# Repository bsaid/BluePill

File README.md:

# BluePill

This project is a mess and it has never been tested.

The goal is to make STM32F103C BluePill compatible PCB with safety resistors, robust power supply with protections and SD card addon using a stacked PCB. The project is designed in [KiCad](https://www.kicad.org/) with design rules for [JLCPCB](https://jlcpcb.com/) including SMT assembly with their LCSC parts library.

This PCB was never tested or manufactured because the STM32 microcontrollers are out of stock globally.

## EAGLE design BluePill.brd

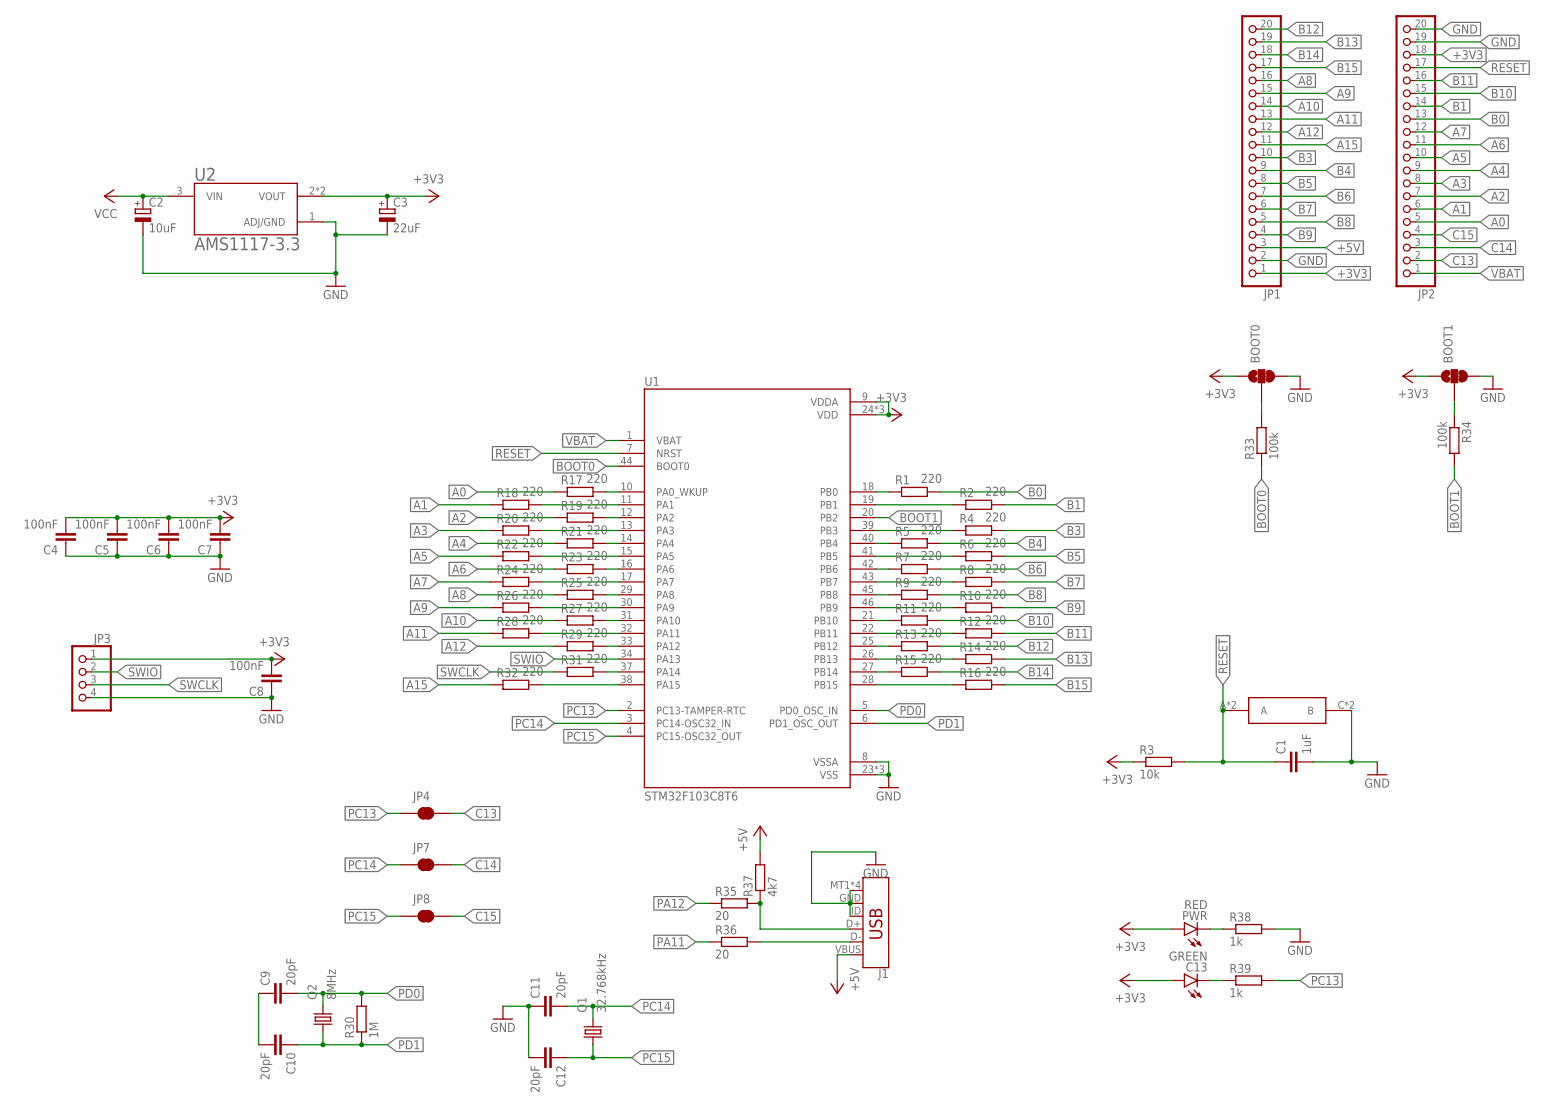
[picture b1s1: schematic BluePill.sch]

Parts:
BOOT0, BOOT1: JUMPER-SMT_3_1-NC_TRACE_NO-SILK; SMT-JUMPER_3_1-NC_TRACE_NO-SILK
C1: 1uF; C0402K; LCSC C52923
C2: 10uF; A/3216-18R; LCSC C7171
C3: 22uF; R/2012-12R; LCSC C147776
C4, C5: 100nF; C0402K; LCSC C1525
C6, C7, C8: 100nF; C0402K; LCSC C52923
C9, C10, C11, C12: 20pF; C0402K; LCSC C52923
C13: GREEN; SML0603; LCSC C72043
J1: USB_MICRO-B_SMT; USB-MICROB
JP1, JP2: PINHD-1X20; 1X20
JP3: PINHD-1X4; 1X04
JP4, JP7, JP8: JUMPER-SMT_2_NC_TRACE_SILK; SMT-JUMPER_2_NC_TRACE_SILK
PWR: RED; SML0603; LCSC C2286
Q1: 32.768kHz; 3.2X1.5; LCSC C32346
Q2: 8MHz; 5.0X3.2_2; LCSC C115962
R1, R2, R4, R5, R6, R7, R8, R9, R10, R11, R12, R13, R14, R15, R16, R17, R18, R19, R20, R21, R22, R23, R24, R25, R26, R27, R28, R29, R31, R32: 220; R0402; LCSC C25091
R3: 10k; R0402; LCSC C25744
R30: 1M; R0402; LCSC C26083
R33, R34: 100k; R0402; LCSC C25741
R35, R36: 20; R0402; LCSC C4109
R37: 4k7; R0402; LCSC C25900
R38, R39: 1k; R0402; LCSC C11702
U1: STM32F103C8T6; QFP50P900X900X160-48N
U2: AMS1117-3.3; SOT229P700X180-4N; LCSC C6186
U$1: TACTILE-SWITCH; TS-1187A-B-A-B; LCSC C318884

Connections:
+3V3: BOOT0.1, BOOT1.1, C3.+, C4.2, C5.2, C6.2, C7.2, C8.2, C13.A, JP1.1, JP2.18, JP3.1, PWR.A, R3.1, U1.9 (VDDA), U1.24 (VDD), U1.36 (VDD), U1.48 (VDD), U2.2 (VOUT), U2.4 (VOUT)
+5V: J1.VBUS, JP1.3, R37.2
A0: JP2.5, R17.1
A1: JP2.6, R18.1
A2: JP2.7, R19.1
A3: JP2.8, R20.1
A4: JP2.9, R21.1
A5: JP2.10, R22.1
A6: JP2.11, R23.1
A7: JP2.12, R24.1
A8: JP1.16, R25.1
A9: JP1.15, R26.1
A10: JP1.14, R27.1
A11: JP1.13, R28.1
A12: JP1.12, R29.1
A15: JP1.11, R32.1
B0: JP2.13, R1.2
B1: JP2.14, R2.2
B3: JP1.10, R4.2
B4: JP1.9, R5.2
B5: JP1.8, R6.2
B6: JP1.7, R7.2
B7: JP1.6, R8.2
B8: JP1.5, R9.2
B9: JP1.4, R10.2
B10: JP2.15, R11.2
B11: JP2.16, R12.2
B12: JP1.20, R13.2
B13: JP1.19, R14.2
B14: JP1.18, R15.2
B15: JP1.17, R16.2
BOOT0: R33.1, U1.44 (BOOT0)
BOOT1: R34.2, U1.20 (PB2)
C13: JP2.2, JP4.2
C14: JP2.3, JP7.2
C15: JP2.4, JP8.2
GND: BOOT0.3, BOOT1.3, C1.2, C2.-, C3.-, C4.1, C5.1, C6.1, C7.1, C8.1, C11.1, C12.2, J1.GND, J1.ID, J1.MT1 (SHIELD), J1.MT2 (SHIELD), J1.P$1 (SHIELD), J1.P$2 (SHIELD), JP1.2, JP2.19, JP2.20, JP3.4, R38.2, U1.8 (VSSA), U1.23 (VSS), U1.35 (VSS), U1.47 (VSS), U2.1 (ADJ/GND), U$1.C (B), U$1.D (B)
unnamed: BOOT0.2, R33.2
unnamed: BOOT1.2, R34.1
unnamed: R1.1, U1.18 (PB0)
unnamed: R2.1, U1.19 (PB1)
unnamed: C9.1, C10.2
unnamed: R4.1, U1.39 (PB3)
unnamed: R5.1, U1.40 (PB4)
unnamed: R6.1, U1.41 (PB5)
unnamed: R7.1, U1.42 (PB6)
unnamed: R8.1, U1.43 (PB7)
unnamed: R9.1, U1.45 (PB8)
unnamed: R10.1, U1.46 (PB9)
unnamed: R11.1, U1.21 (PB10)
unnamed: R12.1, U1.22 (PB11)
unnamed: R13.1, U1.25 (PB12)
unnamed: R14.1, U1.26 (PB13)
unnamed: R15.1, U1.27 (PB14)
unnamed: R16.1, U1.28 (PB15)
unnamed: PWR.C, R38.1
unnamed: C13.C, R39.1
unnamed: J1.D-, R36.2
unnamed: R17.2, U1.10 (PA0_WKUP)
unnamed: R18.2, U1.11 (PA1)
unnamed: R19.2, U1.12 (PA2)
unnamed: R20.2, U1.13 (PA3)
unnamed: R21.2, U1.14 (PA4)
unnamed: R22.2, U1.15 (PA5)
unnamed: R23.2, U1.16 (PA6)
unnamed: R24.2, U1.17 (PA7)
unnamed: R25.2, U1.29 (PA8)
unnamed: R26.2, U1.30 (PA9)
unnamed: R27.2, U1.31 (PA10)
unnamed: R31.2, U1.37 (PA14)
unnamed: R32.2, U1.38 (PA15)
unnamed: J1.D+, R35.2, R37.1
PA11: R28.2, R36.1, U1.32 (PA11)
PA12: R29.2, R35.1, U1.33 (PA12)
PC13: JP4.1, R39.2, U1.2 (PC13-TAMPER-RTC)
PC14: C11.2, JP7.1, Q1.2, U1.3 (PC14-OSC32_IN)
PC15: C12.1, JP8.1, Q1.1, U1.4 (PC15-OSC32_OUT)
PD0: C9.2, Q2.2, R30.2, U1.5 (PD0_OSC_IN)
PD1: C10.1, Q2.1, R30.1, U1.6 (PD1_OSC_OUT)
RESET: C1.1, JP2.17, R3.2, U1.7 (NRST), U$1.A, U$1.B (A)
SWCLK: JP3.3, R31.1
SWIO: JP3.2, U1.34 (PA13)
VBAT: JP2.1, U1.1 (VBAT)
VCC: C2.+, U2.3 (VIN)

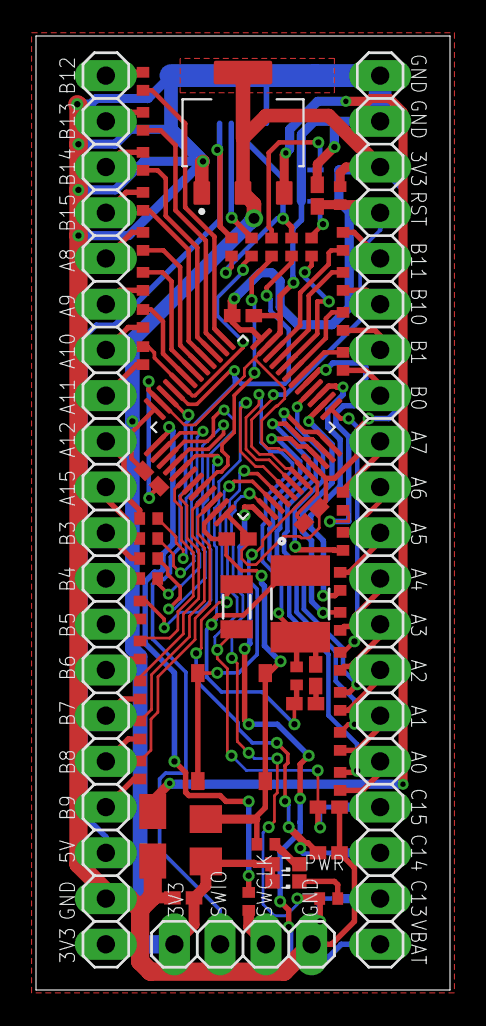
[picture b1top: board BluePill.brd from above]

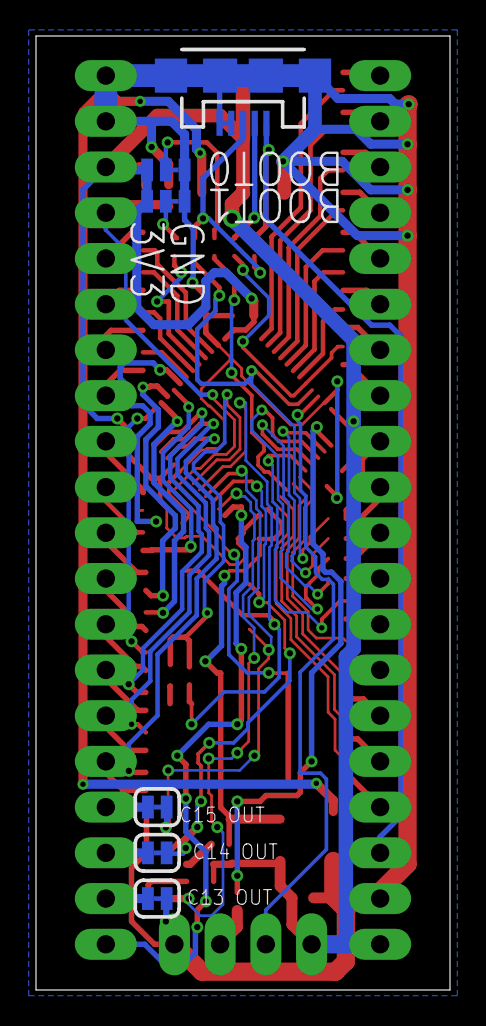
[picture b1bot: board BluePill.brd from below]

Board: 2 copper layers, 23.0 x 53.0 mm, 67 parts (6 on the bottom side), 84 nets.

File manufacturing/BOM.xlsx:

Comment | Designator | Footprint | LCSC
100k | R33, R34 | R0402 | C25741
100nF | C4, C5 | C0402K | C1525
100nF | C6, C7, C8 | C0402K | C52923
10k | R3 | R0402 | C25744
10uF | C2 | CASE-A_3216 | C7171
1M | R30 | R0402 | C26083
1k | R38, R39 | R0402 | C11702
1uF | C1 | C0402K | C52923
20 | R35, R36 | R0402 | C4109
20pF | C9, C10, C11, C12 | C0402K | C52923
220 | R1, R2, R4, R5, R6, R7, R8, R9, R10, R11, R12, R13, R14, R15, R16, R17, R18, R1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 | R0402 | C25091
22uF | C3 | CASE-R_2012 | C147776
32.768kHz | Q1 | SMD-3215_2P | C32346
4k7 | R37 | R0402 | C25900
8MHz | Q2 | SMD-5032_2P | C115962
AMS1117-3.3 | U2 | SOT-223 | C6186
GREEN | C13 | LED_0603 | C72043
RED | PWR | LED_0603 | C2286
STM32F103C8T6 | U1 | LQFP-48_7.0x7.0x0.5P | C8734
TACTILE-SWITCH | U$1 | SMD-SW-4_5.1x5.1x1.5 | C318884

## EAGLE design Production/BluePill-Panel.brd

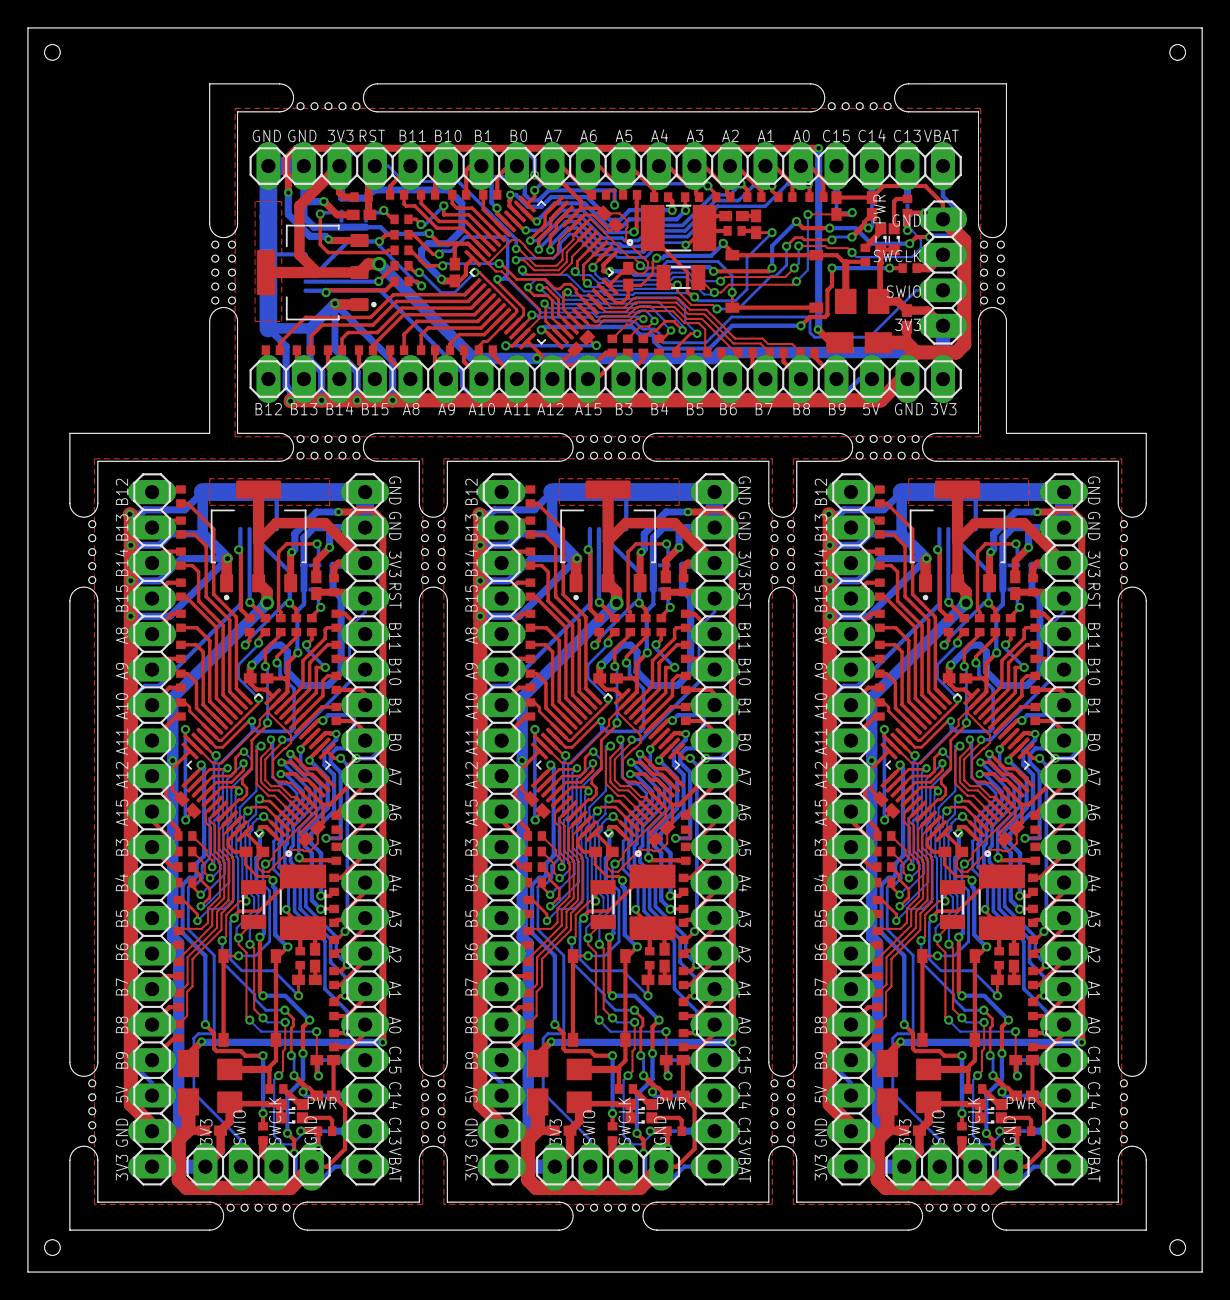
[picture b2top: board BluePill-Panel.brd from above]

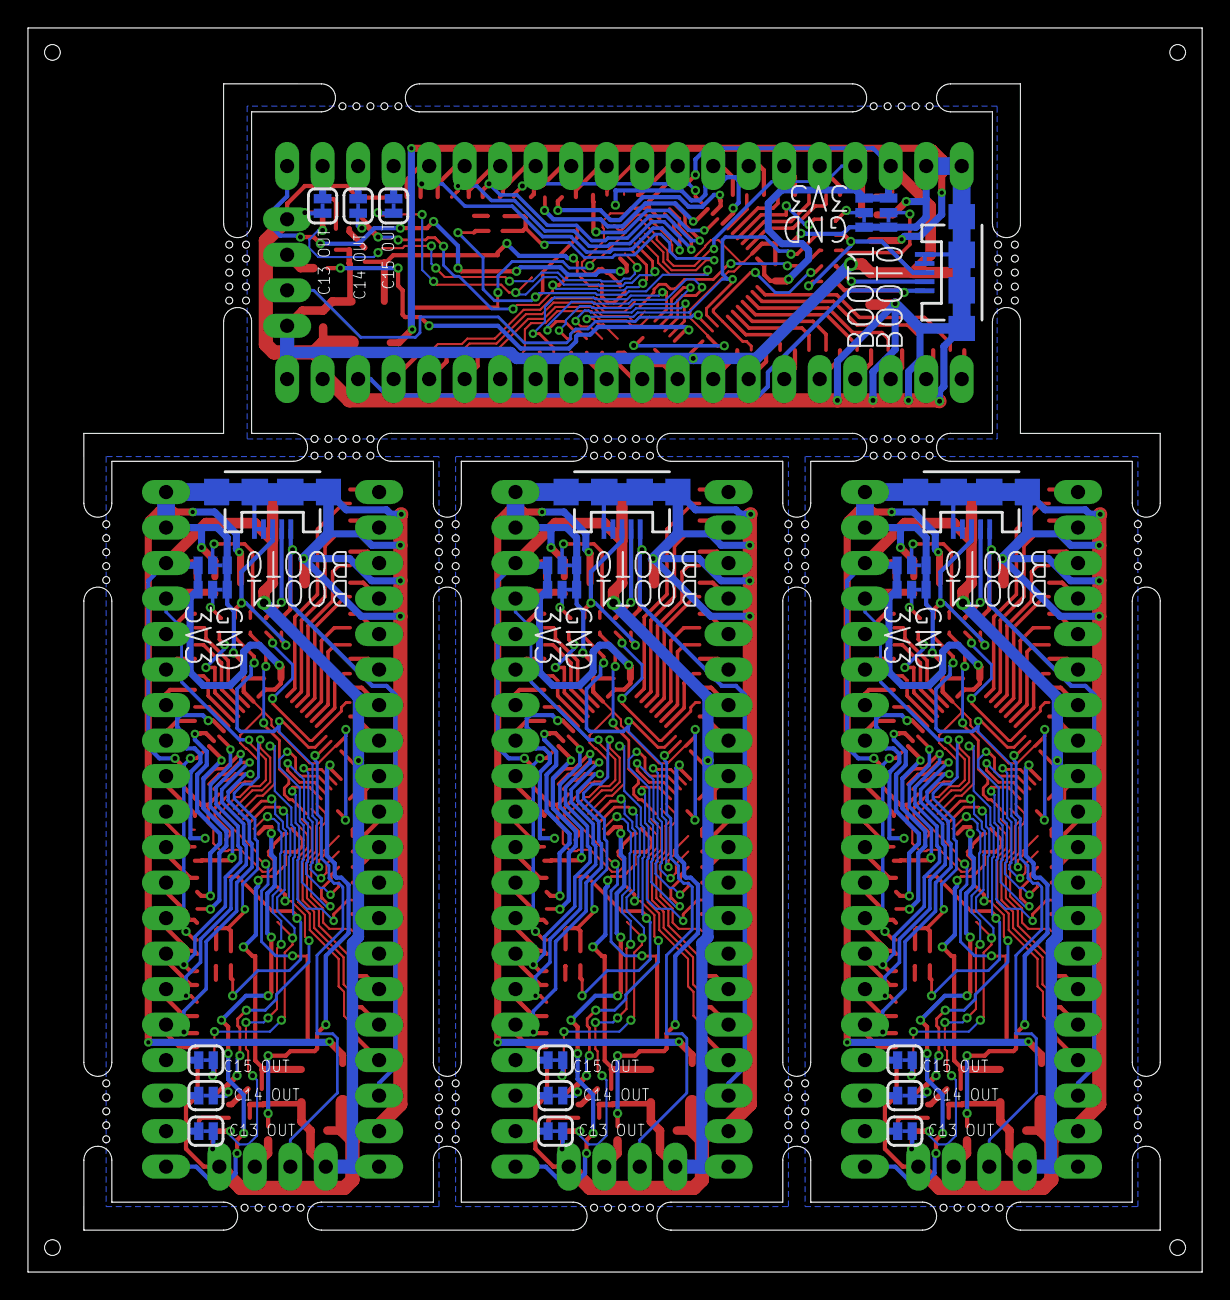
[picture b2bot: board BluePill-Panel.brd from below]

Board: 2 copper layers, 84.0 x 89.0 mm, 268 parts (24 on the bottom side), 336 nets.

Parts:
BOOT0, BOOT1, BOOT2, BOOT3, BOOT4, BOOT5, BOOT6, BOOT7: JUMPER-SMT_3_1-NC_TRACE_NO-SILK; SMT-JUMPER_3_1-NC_TRACE_NO-SILK
C1, C14, C27, C40: 1uF; C0402K
C2, C16, C29, C42: 10uF; A/3216-18R
C3, C15, C28, C41: 22uF; R/2012-12R
C4, C5, C6, C7, C8, C17, C18, C19, C20, C21, C30, C31, C32, C33, C34, C43, C44, C45, C46, C47: 100nF; C0402K
C9, C10, C11, C12, C22, C23, C24, C25, C35, C36, C37, C38, C48, C49, C50, C51: 20pF; C0402K
C13, C26, C39, C52: GREEN; SML0603
J1, J2, J3, J4: USB-MICROB
JP1, JP2, JP5, JP6, JP13, JP14, JP19, JP20: 1X20
JP3, JP9, JP15, JP21: 1X04
JP4, JP7, JP8, JP10, JP11, JP12, JP16, JP17, JP18, JP22, JP23, JP24: JUMPER-SMT_2_NC_TRACE_SILK; SMT-JUMPER_2_NC_TRACE_SILK
PWR, PWR1, PWR2, PWR3: RED; SML0603
Q1, Q3, Q5, Q7: 32.768kHz; 3.2X1.5
Q2, Q4, Q6, Q8: 8MHz; 5.0X3.2_2
R1, R2, R4, R5, R6, R7, R8, R9, R10, R11, R12, R13, R14, R15, R16, R17, R18, R19, R20, R21, R22, R23, R24, R25, R26, R27, R28, R29, R31, R32, R40, R41, R42, R43, R44, R45, R46, R47, R48, R49, R50, R51, R52, R53, R54, R55, R56, R57, R58, R59, R60, R61, R62, R63, R64, R65, R66, R67, R68, R69, R79, R80, R81, R82, R83, R84, R85, R86, R87, R88, R89, R90, R91, R92, R93, R94, R95, R96, R97, R98, R99, R100, R101, R102, R103, R104, R105, R106, R107, R108, R118, R119, R120, R121, R122, R123, R124, R125, R126, R127, R128, R129, R130, R131, R132, R133, R134, R135, R136, R137, R138, R139, R140, R141, R142, R143, R144, R145, R146, R147: 220; R0402
R3, R72, R111, R150: 10k; R0402
R30, R76, R115, R154: 1M; R0402
R33, R34, R70, R71, R109, R110, R148, R149: 100k; R0402
R35, R36, R73, R74, R112, R113, R151, R152: 20; R0402
R37, R75, R114, R153: 4k7; R0402
R38, R39, R77, R78, R116, R117, R155, R156: 1k; R0402
U1, U3, U5, U7: STM32F103C8T6; QFP50P900X900X160-48N
U2, U4, U6, U8: AMS1117-3.3; SOT229P700X180-4N
U$1, U$2, U$3, U$4: TACTILE-SWITCH; TS-1187A-B-A-B

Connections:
+3V1: BOOT2.1, BOOT3.1, C15.+, C17.2, C18.2, C19.2, C20.2, C21.2, C26.A, JP5.1, JP6.18, JP9.1, PWR1.A, R72.1, U3.9, U3.24, U3.36, U3.48, U4.2, U4.4
+3V2: BOOT4.1, BOOT5.1, C28.+, C30.2, C31.2, C32.2, C33.2, C34.2, C39.A, JP13.1, JP14.18, JP15.1, PWR2.A, R111.1, U5.9, U5.24, U5.36, U5.48, U6.2, U6.4
+3V3: BOOT0.1, BOOT1.1, C3.+, C4.2, C5.2, C6.2, C7.2, C8.2, C13.A, JP1.1, JP2.18, JP3.1, PWR.A, R3.1, U1.9, U1.24, U1.36, U1.48, U2.2, U2.4
+3V4: BOOT6.1, BOOT7.1, C41.+, C43.2, C44.2, C45.2, C46.2, C47.2, C52.A, JP19.1, JP20.18, JP21.1, PWR3.A, R150.1, U7.9, U7.24, U7.36, U7.48, U8.2, U8.4
+5V: J1.VBUS, JP1.3, R37.2
+5V1: J2.VBUS, JP5.3, R75.2
+5V2: J3.VBUS, JP13.3, R114.2
+5V3: J4.VBUS, JP19.3, R153.2
A0: JP2.5, R17.1
A1: JP2.6, R18.1
A2: JP2.7, R19.1
A3: JP2.8, R20.1
A4: JP2.9, R21.1
A5: JP2.10, R22.1
A6: JP2.11, R23.1
A7: JP2.12, R24.1
A8: JP1.16, R25.1
A9: JP1.15, R26.1
A10: JP1.14, R27.1
A11: JP1.13, R28.1
A12: JP1.12, R29.1
A13: JP6.5, R55.1
A14: JP6.7, R57.1
A15: JP1.11, R32.1
A16: JP6.9, R59.1
A17: JP6.11, R61.1
A18: JP5.16, R63.1
A19: JP5.14, R65.1
A20: JP5.12, R67.1
A21: JP6.6, R56.1
A22: JP6.8, R58.1
A23: JP6.10, R60.1
A24: JP6.12, R62.1
A25: JP5.15, R64.1
A26: JP5.13, R66.1
A27: JP5.11, R69.1
A28: JP14.5, R94.1
A29: JP14.7, R96.1
A30: JP14.9, R98.1
A31: JP14.11, R100.1
A32: JP13.16, R102.1
A33: JP13.14, R104.1
A34: JP13.12, R106.1
A35: JP14.6, R95.1
A36: JP14.8, R97.1
A37: JP14.10, R99.1
A38: JP14.12, R101.1
A39: JP13.15, R103.1
A40: JP13.13, R105.1
A41: JP13.11, R108.1
A42: JP20.5, R133.1
A43: JP20.7, R135.1
A44: JP20.9, R137.1
A45: JP20.11, R139.1
A46: JP19.16, R141.1
A47: JP19.14, R143.1
A48: JP19.12, R145.1
A49: JP20.6, R134.1
A50: JP20.8, R136.1
A51: JP20.10, R138.1
A52: JP20.12, R140.1
A53: JP19.15, R142.1
A54: JP19.13, R144.1
A55: JP19.11, R147.1
B0: JP2.13, R1.2
B1: JP2.14, R2.2
B2: JP6.13, R40.2
B3: JP1.10, R4.2
B4: JP1.9, R5.2
B5: JP1.8, R6.2
B6: JP1.7, R7.2
B7: JP1.6, R8.2
B8: JP1.5, R9.2
B9: JP1.4, R10.2
B10: JP2.15, R11.2
B11: JP2.16, R12.2
B12: JP1.20, R13.2
B13: JP1.19, R14.2
B14: JP1.18, R15.2
B15: JP1.17, R16.2
B16: JP6.14, R41.2
B17: JP5.10, R42.2
B18: JP5.9, R43.2
B19: JP5.7, R45.2
B20: JP5.8, R44.2
B21: JP5.6, R46.2
B22: JP5.5, R47.2
B23: JP6.15, R49.2
B24: JP5.4, R48.2
B25: JP5.20, R51.2
B26: JP6.16, R50.2
B27: JP5.19, R52.2
B28: JP5.18, R53.2
B29: JP5.17, R54.2
B30: JP14.13, R79.2
B31: JP14.14, R80.2
B32: JP13.10, R81.2
B33: JP13.9, R82.2
B34: JP13.7, R84.2
B35: JP13.8, R83.2
B36: JP13.6, R85.2
B37: JP13.5, R86.2
B38: JP14.15, R88.2
B39: JP13.4, R87.2
B40: JP13.20, R90.2
B41: JP14.16, R89.2
B42: JP13.19, R91.2
B43: JP13.18, R92.2
B44: JP13.17, R93.2
B45: JP20.13, R118.2
B46: JP20.14, R119.2
B47: JP19.10, R120.2
B48: JP19.9, R121.2
B49: JP19.7, R123.2
B50: JP19.8, R122.2
B51: JP19.6, R124.2
B52: JP19.5, R125.2
B53: JP20.15, R127.2
B54: JP19.4, R126.2
B55: JP19.20, R129.2
B56: JP20.16, R128.2
B57: JP19.19, R130.2
B58: JP19.18, R131.2
B59: JP19.17, R132.2
BOOT0: R33.1, U1.44
BOOT1: R34.2, U1.20
BOOT2: R70.1, U3.44
BOOT3: R71.2, U3.20
BOOT4: R109.1, U5.44
BOOT5: R110.2, U5.20
BOOT6: R148.1, U7.44
BOOT7: R149.2, U7.20
C1: JP6.4, JP12.2
C2: JP6.2, JP10.2
C3: JP6.3, JP11.2
C4: JP14.4, JP18.2
C5: JP14.2, JP16.2
C6: JP14.3, JP17.2
C7: JP20.4, JP24.2
C8: JP20.2, JP22.2
C9: JP20.3, JP23.2
C13: JP2.2, JP4.2
C14: JP2.3, JP7.2
C15: JP2.4, JP8.2
GND: BOOT0.3, BOOT1.3, C1.2, C2.-, C3.-, C4.1, C5.1, C6.1, C7.1, C8.1, C11.1, C12.2, J1.GND, J1.ID, J1.MT1, J1.MT2, J1.P$1, J1.P$2, JP1.2, JP2.19, JP2.20, JP3.4, R38.2, U1.8, U1.23, U1.35, U1.47, U2.1, U$1.C, U$1.D
GND1: BOOT2.3, BOOT3.3, C14.2, C15.-, C16.-, C17.1, C18.1, C19.1, C20.1, C21.1, C24.1, C25.2, J2.GND, J2.ID, J2.MT1, J2.MT2, J2.P$1, J2.P$2, JP5.2, JP6.19, JP6.20, JP9.4, R77.2, U3.8, U3.23, U3.35, U3.47, U4.1, U$2.C, U$2.D
GND2: BOOT4.3, BOOT5.3, C27.2, C28.-, C29.-, C30.1, C31.1, C32.1, C33.1, C34.1, C37.1, C38.2, J3.GND, J3.ID, J3.MT1, J3.MT2, J3.P$1, J3.P$2, JP13.2, JP14.19, JP14.20, JP15.4, R116.2, U5.8, U5.23, U5.35, U5.47, U6.1, U$3.C, U$3.D
GND3: BOOT6.3, BOOT7.3, C40.2, C41.-, C42.-, C43.1, C44.1, C45.1, C46.1, C47.1, C50.1, C51.2, J4.GND, J4.ID, J4.MT1, J4.MT2, J4.P$1, J4.P$2, JP19.2, JP20.19, JP20.20, JP21.4, R155.2, U7.8, U7.23, U7.35, U7.47, U8.1, U$4.C, U$4.D
unnamed: BOOT0.2, R33.2
unnamed: BOOT1.2, R34.1
unnamed: R1.1, U1.18
unnamed: R2.1, U1.19
unnamed: C9.1, C10.2
unnamed: R4.1, U1.39
unnamed: R5.1, U1.40
unnamed: R6.1, U1.41
unnamed: R7.1, U1.42
unnamed: R8.1, U1.43
unnamed: R9.1, U1.45
unnamed: R10.1, U1.46
unnamed: R11.1, U1.21
unnamed: R12.1, U1.22
unnamed: R13.1, U1.25
unnamed: R14.1, U1.26
unnamed: R15.1, U1.27
unnamed: R16.1, U1.28
unnamed: PWR.C, R38.1
unnamed: C13.C, R39.1
unnamed: R40.1, U3.18
unnamed: R41.1, U3.19
unnamed: R42.1, U3.39
unnamed: R43.1, U3.40
unnamed: J1.D-, R36.2
unnamed: R17.2, U1.10
unnamed: R18.2, U1.11
unnamed: R19.2, U1.12
unnamed: R20.2, U1.13
unnamed: R21.2, U1.14
unnamed: R22.2, U1.15
unnamed: R23.2, U1.16
unnamed: R24.2, U1.17
unnamed: R25.2, U1.29
unnamed: R26.2, U1.30
unnamed: R27.2, U1.31
unnamed: R44.1, U3.41
unnamed: R45.1, U3.42
unnamed: R46.1, U3.43
unnamed: R31.2, U1.37
unnamed: R32.2, U1.38
unnamed: R47.1, U3.45
unnamed: R48.1, U3.46
unnamed: R49.1, U3.21
unnamed: J1.D+, R35.2, R37.1
unnamed: R50.1, U3.22
unnamed: R51.1, U3.25
unnamed: R52.1, U3.26
unnamed: R53.1, U3.27
unnamed: R54.1, U3.28
unnamed: R55.2, U3.10
unnamed: R56.2, U3.11
unnamed: R57.2, U3.12
unnamed: R58.2, U3.13
unnamed: R59.2, U3.14
unnamed: R60.2, U3.15
unnamed: R61.2, U3.16
unnamed: R62.2, U3.17
unnamed: R63.2, U3.29
unnamed: R64.2, U3.30
unnamed: R65.2, U3.31
unnamed: R68.2, U3.37
unnamed: R69.2, U3.38
unnamed: BOOT2.2, R70.2
unnamed: BOOT3.2, R71.1
unnamed: J2.D-, R74.2
unnamed: J2.D+, R73.2, R75.1
unnamed: C22.1, C23.2
unnamed: PWR1.C, R77.1
unnamed: C26.C, R78.1
unnamed: R79.1, U5.18
unnamed: R80.1, U5.19
unnamed: R81.1, U5.39
unnamed: R82.1, U5.40
unnamed: R83.1, U5.41
unnamed: R84.1, U5.42
unnamed: R85.1, U5.43
unnamed: R86.1, U5.45
unnamed: R87.1, U5.46
unnamed: R88.1, U5.21
unnamed: R89.1, U5.22
unnamed: R90.1, U5.25
unnamed: R91.1, U5.26
unnamed: R92.1, U5.27
unnamed: R93.1, U5.28
unnamed: R94.2, U5.10
unnamed: R95.2, U5.11
unnamed: R96.2, U5.12
unnamed: R97.2, U5.13
unnamed: R98.2, U5.14
unnamed: R99.2, U5.15
unnamed: R100.2, U5.16
unnamed: R101.2, U5.17
unnamed: R102.2, U5.29
unnamed: R103.2, U5.30
unnamed: R104.2, U5.31
unnamed: R107.2, U5.37
unnamed: R108.2, U5.38
unnamed: BOOT4.2, R109.2
unnamed: BOOT5.2, R110.1
unnamed: J3.D-, R113.2
unnamed: J3.D+, R112.2, R114.1
unnamed: C35.1, C36.2
unnamed: PWR2.C, R116.1
unnamed: C39.C, R117.1
unnamed: R118.1, U7.18
unnamed: R119.1, U7.19
unnamed: R120.1, U7.39
unnamed: R121.1, U7.40
unnamed: R122.1, U7.41
unnamed: R123.1, U7.42
unnamed: R124.1, U7.43
unnamed: R125.1, U7.45
unnamed: R126.1, U7.46
unnamed: R127.1, U7.21
unnamed: R128.1, U7.22
unnamed: R129.1, U7.25
unnamed: R130.1, U7.26
unnamed: R131.1, U7.27
unnamed: R132.1, U7.28
unnamed: R133.2, U7.10
unnamed: R134.2, U7.11
unnamed: R135.2, U7.12
unnamed: R136.2, U7.13
unnamed: R137.2, U7.14
unnamed: R138.2, U7.15
unnamed: R139.2, U7.16
unnamed: R140.2, U7.17
unnamed: R141.2, U7.29
unnamed: R142.2, U7.30
unnamed: R143.2, U7.31
unnamed: R146.2, U7.37
unnamed: R147.2, U7.38
unnamed: BOOT6.2, R148.2
unnamed: BOOT7.2, R149.1
unnamed: J4.D-, R152.2
unnamed: J4.D+, R151.2, R153.1
unnamed: C48.1, C49.2
unnamed: PWR3.C, R155.1
unnamed: C52.C, R156.1
PA1: R66.2, R74.1, U3.32
PA2: R67.2, R73.1, U3.33
PA3: R105.2, R113.1, U5.32
PA4: R106.2, R112.1, U5.33
PA5: R144.2, R152.1, U7.32
PA6: R145.2, R151.1, U7.33
PA11: R28.2, R36.1, U1.32
PA12: R29.2, R35.1, U1.33
PC1: JP10.1, R78.2, U3.2
PC2: C24.2, JP11.1, Q3.2, U3.3
PC3: C25.1, JP12.1, Q3.1, U3.4
PC4: JP16.1, R117.2, U5.2
PC5: C37.2, JP17.1, Q5.2, U5.3
PC6: C38.1, JP18.1, Q5.1, U5.4
PC7: JP22.1, R156.2, U7.2
PC8: C50.2, JP23.1, Q7.2, U7.3
PC9: C51.1, JP24.1, Q7.1, U7.4
PC13: JP4.1, R39.2, U1.2
PC14: C11.2, JP7.1, Q1.2, U1.3
PC15: C12.1, JP8.1, Q1.1, U1.4
PD0: C9.2, Q2.2, R30.2, U1.5
PD1: C10.1, Q2.1, R30.1, U1.6
PD2: C22.2, Q4.2, R76.2, U3.5
PD3: C23.1, Q4.1, R76.1, U3.6
PD4: C35.2, Q6.2, R115.2, U5.5
PD5: C36.1, Q6.1, R115.1, U5.6
PD6: C48.2, Q8.2, R154.2, U7.5
PD7: C49.1, Q8.1, R154.1, U7.6
RESET: C1.1, JP2.17, R3.2, U1.7, U$1.A, U$1.B
RESET1: C14.1, JP6.17, R72.2, U3.7, U$2.A, U$2.B
RESET2: C27.1, JP14.17, R111.2, U5.7, U$3.A, U$3.B
RESET3: C40.1, JP20.17, R150.2, U7.7, U$4.A, U$4.B
SWCLK: JP3.3, R31.1
SWCLK1: JP9.3, R68.1
SWCLK2: JP15.3, R107.1
SWCLK3: JP21.3, R146.1
SWIO: JP3.2, U1.34
SWIO1: JP9.2, U3.34
SWIO2: JP15.2, U5.34
SWIO3: JP21.2, U7.34
VBAT: JP2.1, U1.1
VBAT1: JP6.1, U3.1
VBAT2: JP14.1, U5.1
VBAT3: JP20.1, U7.1
VCC: C2.+, U2.3
VCC1: C16.+, U4.3
VCC2: C29.+, U6.3
VCC3: C42.+, U8.3

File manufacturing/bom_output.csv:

Qty, PROD_ID, Names, Value, Package
4, , C1; C14; C27; C40, 1uF, C0402K
4, , C2; C16; C29; C42, 10uF, A/3216-18R
4, , C3; C15; C28; C41, 22uF, R/2012-12R
20, , C4; C5; C6; C7; C8; C17; C18; C19; C20; C21; C30; C31; C32; C33; C34; C43; C44; C45; C46; C47, 100nF, C0402K
16, , C9; C10; C11; C12; C22; C23; C24; C25; C35; C36; C37; C38; C48; C49; C50; C51, 20pF, C0402K
4, , C13; C26; C39; C52, GREEN, SML0603
4, , PWR; PWR1; PWR2; PWR3, RED, SML0603
4, , Q1; Q3; Q5; Q7, 32.768kHz, 3.2X1.5
4, , Q2; Q4; Q6; Q8, 8MHz, 5.0X3.2_2
120, , R1; R2; R4; R5; R6; R7; R8; R9; R10; R11; R12; R13; R14; R15; R16; R17; R18; R19; R20; R21; R22; R23; R24; R25; R26; R27; R28; R29; R31; R32; R40; R41; R42; R43; R44; R45; R46; R47; R48; R49; R50; R51; R52; R53; R54; R55; R56; R57; R58; R59; R60; R61; R62; R63; R64; R65; R66; R67; R68; R69; R79; R80; R81; R82; R83; R84; R85; R86; R87; R88; R89; R90; R91; R92; R93; R94; R95; R96; R97; R98; R99; R100; R101; R102; R103; R104; R105; R106; R107; R108; R118; R119; R120; R121; R122; R123; R124; R125; R126; R127; R128; R129; R130; R131; R132; R133; R134; R135; R136; R137; R138; R139; R140; R141; R142; R143; R144; R145; R146; R147, 220, R0402
4, , R3; R72; R111; R150, 10k, R0402
4, , R30; R76; R115; R154, 1M, R0402
8, , R33; R34; R70; R71; R109; R110; R148; R149, 100k, R0402
8, , R35; R36; R73; R74; R112; R113; R151; R152, 20, R0402
4, , R37; R75; R114; R153, 4k7, R0402
8, , R38; R39; R77; R78; R116; R117; R155; R156, 1k, R0402
4, , U$1; U$2; U$3; U$4, TACTILE-SWITCH, TS-1187A-B-A-B
4, , U1; U3; U5; U7, STM32F103C8T6, QFP50P900X900X160-48N
4, , U2; U4; U6; U8, AMS1117-3.3, SOT229P700X180-4N

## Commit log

2020-09-12 Initial commit.
2020-09-16 Fix some warnings
2020-09-17 Generate cam
2020-09-19 Add paneled version
2020-09-19 Finish panelized version
2020-09-19 Generate new gerber files
2021-03-02 Switch to KiCad
2021-03-21 Finish schematic
2021-03-21 Add LCSC numbers
2021-03-23 Route board
2022-04-08 Added 3D render of the PCB.

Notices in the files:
parts and their libraries:
SparkFun-Jumpers: Licensing: Creative Commons ShareAlike 4.0 International - https://creativecommons.org/licenses/by-sa/4.0
crystal-geyer_V1_0: Copyright: Geyer-Electronic
